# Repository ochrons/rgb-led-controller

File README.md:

rgb-led-controller
==================

Multi node controller for RGB LED strips

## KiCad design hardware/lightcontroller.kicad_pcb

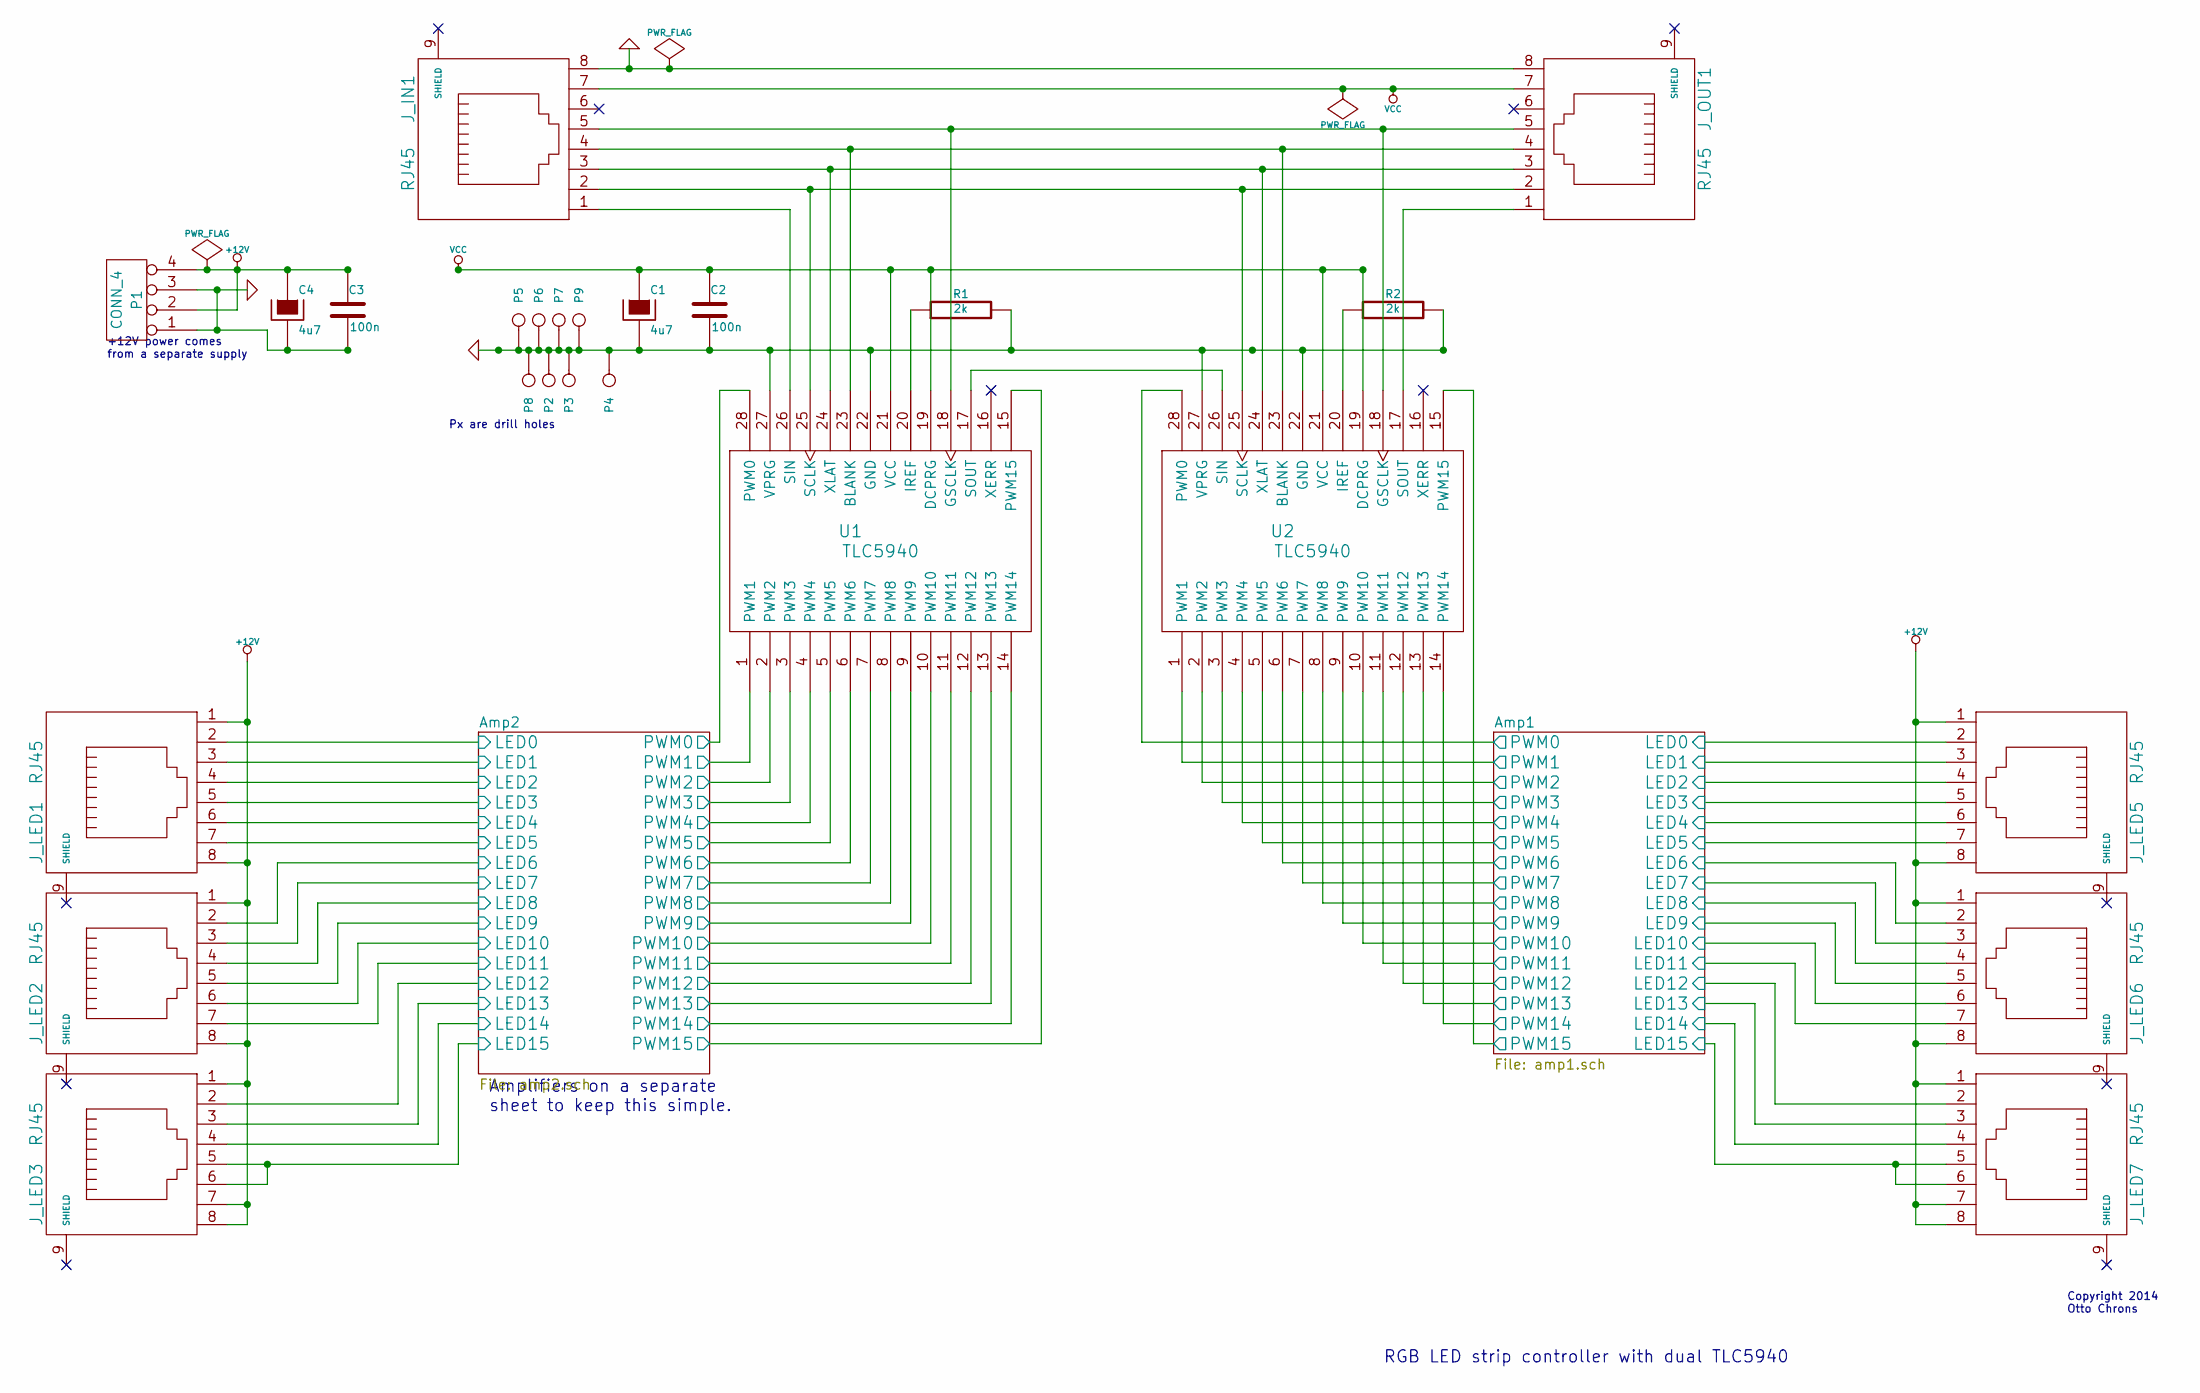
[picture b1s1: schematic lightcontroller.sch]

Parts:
C1, C4: 4u7
C2, C3: 100n
J_IN1: RJ45
J_LED1, J_LED2, J_LED3, J_LED5, J_LED6, J_LED7: RJ45
J_OUT1: RJ45
P1: CONN_4
P2, P3, P4, P6, P7, P9: CONN_1
P5, P8: CONN_1
R1, R2: 2k
U1, U2: TLC5940

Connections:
+12V: C3.1, C4.1, J_LED1.1, J_LED1.8, J_LED2.1, J_LED2.8, J_LED3.1, J_LED3.7, J_LED3.8, J_LED5.1, J_LED5.8, J_LED6.1, J_LED6.8, J_LED7.1, J_LED7.7, J_LED7.8, P1.2, P1.4; also elsewhere on the board
/Amp1/LED0: J_LED5.2; also elsewhere on the board
/Amp1/LED1: J_LED5.3; also elsewhere on the board
/Amp1/LED2: J_LED5.4; also elsewhere on the board
/Amp1/LED3: J_LED5.5; also elsewhere on the board
/Amp1/LED4: J_LED5.6; also elsewhere on the board
/Amp1/LED5: J_LED5.7; also elsewhere on the board
/Amp1/LED6: J_LED6.2; also elsewhere on the board
/Amp1/LED7: J_LED6.3; also elsewhere on the board
/Amp1/LED8: J_LED6.4; also elsewhere on the board
/Amp1/LED9: J_LED6.5; also elsewhere on the board
/Amp1/LED10: J_LED6.6; also elsewhere on the board
/Amp1/LED11: J_LED6.7; also elsewhere on the board
/Amp1/LED12: J_LED7.2; also elsewhere on the board
/Amp1/LED13: J_LED7.3; also elsewhere on the board
/Amp1/LED14: J_LED7.4; also elsewhere on the board
/Amp1/LED15: J_LED7.5, J_LED7.6; also elsewhere on the board
/Amp1/PWM0: U2.28 (PWM0); also elsewhere on the board
/Amp1/PWM1: U2.1 (PWM1); also elsewhere on the board
/Amp1/PWM2: U2.2 (PWM2); also elsewhere on the board
/Amp1/PWM3: U2.3 (PWM3); also elsewhere on the board
/Amp1/PWM4: U2.4 (PWM4); also elsewhere on the board
/Amp1/PWM5: U2.5 (PWM5); also elsewhere on the board
/Amp1/PWM6: U2.6 (PWM6); also elsewhere on the board
/Amp1/PWM7: U2.7 (PWM7); also elsewhere on the board
/Amp1/PWM8: U2.8 (PWM8); also elsewhere on the board
/Amp1/PWM9: U2.9 (PWM9); also elsewhere on the board
/Amp1/PWM10: U2.10 (PWM10); also elsewhere on the board
/Amp1/PWM11: U2.11 (PWM11); also elsewhere on the board
/Amp1/PWM12: U2.12 (PWM12); also elsewhere on the board
/Amp1/PWM13: U2.13 (PWM13); also elsewhere on the board
/Amp1/PWM14: U2.14 (PWM14); also elsewhere on the board
/Amp1/PWM15: U2.15 (PWM15); also elsewhere on the board
/Amp2/LED0: J_LED1.2; also elsewhere on the board
/Amp2/LED1: J_LED1.3; also elsewhere on the board
/Amp2/LED2: J_LED1.4; also elsewhere on the board
/Amp2/LED3: J_LED1.5; also elsewhere on the board
/Amp2/LED4: J_LED1.6; also elsewhere on the board
/Amp2/LED5: J_LED1.7; also elsewhere on the board
/Amp2/LED6: J_LED2.2; also elsewhere on the board
/Amp2/LED7: J_LED2.3; also elsewhere on the board
/Amp2/LED8: J_LED2.4; also elsewhere on the board
/Amp2/LED9: J_LED2.5; also elsewhere on the board
/Amp2/LED10: J_LED2.6; also elsewhere on the board
/Amp2/LED11: J_LED2.7; also elsewhere on the board
/Amp2/LED12: J_LED3.2; also elsewhere on the board
/Amp2/LED13: J_LED3.3; also elsewhere on the board
/Amp2/LED14: J_LED3.4; also elsewhere on the board
/Amp2/LED15: J_LED3.5, J_LED3.6; also elsewhere on the board
/Amp2/PWM0: U1.28 (PWM0); also elsewhere on the board
/Amp2/PWM1: U1.1 (PWM1); also elsewhere on the board
/Amp2/PWM2: U1.2 (PWM2); also elsewhere on the board
/Amp2/PWM3: U1.3 (PWM3); also elsewhere on the board
/Amp2/PWM4: U1.4 (PWM4); also elsewhere on the board
/Amp2/PWM5: U1.5 (PWM5); also elsewhere on the board
/Amp2/PWM6: U1.6 (PWM6); also elsewhere on the board
/Amp2/PWM7: U1.7 (PWM7); also elsewhere on the board
/Amp2/PWM8: U1.8 (PWM8); also elsewhere on the board
/Amp2/PWM9: U1.9 (PWM9); also elsewhere on the board
/Amp2/PWM10: U1.10 (PWM10); also elsewhere on the board
/Amp2/PWM11: U1.11 (PWM11); also elsewhere on the board
/Amp2/PWM12: U1.12 (PWM12); also elsewhere on the board
/Amp2/PWM13: U1.13 (PWM13); also elsewhere on the board
/Amp2/PWM14: U1.14 (PWM14); also elsewhere on the board
/Amp2/PWM15: U1.15 (PWM15); also elsewhere on the board
GND: C1.2, C2.2, C3.2, C4.2, J_IN1.8, J_OUT1.8, P1.1, P1.3, P2.1, P3.1, P4.1, P5.1, P6.1, P7.1, P8.1, P9.1, R1.2, R2.2, U1.22 (GND), U1.27 (VPRG), U2.22 (GND), U2.27 (VPRG); also elsewhere on the board
unnamed: J_OUT1.1, U2.17 (SOUT)
unnamed: J_IN1.1, U1.26 (SIN)
unnamed: R1.1, U1.20 (IREF)
unnamed: J_IN1.5, J_OUT1.5, U1.18 (GSCLK), U2.18 (GSCLK)
unnamed: U1.17 (SOUT), U2.26 (SIN)
unnamed: J_IN1.4, J_OUT1.4, U1.23 (BLANK), U2.23 (BLANK)
unnamed: R2.1, U2.20 (IREF)
unnamed: J_IN1.3, J_OUT1.3, U1.24 (XLAT), U2.24 (XLAT)
unnamed: J_IN1.2, J_OUT1.2, U1.25 (SCLK), U2.25 (SCLK)
VCC: C1.1, C2.1, J_IN1.7, J_OUT1.7, U1.19 (DCPRG), U1.21 (VCC), U2.19 (DCPRG), U2.21 (VCC)

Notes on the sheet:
RGB LED strip controller with dual TLC5940
Px are drill holes
Amplifiers on a separate sheet to keep this simple.
+12V power comes from a separate supply
Copyright 2014 Otto Chrons

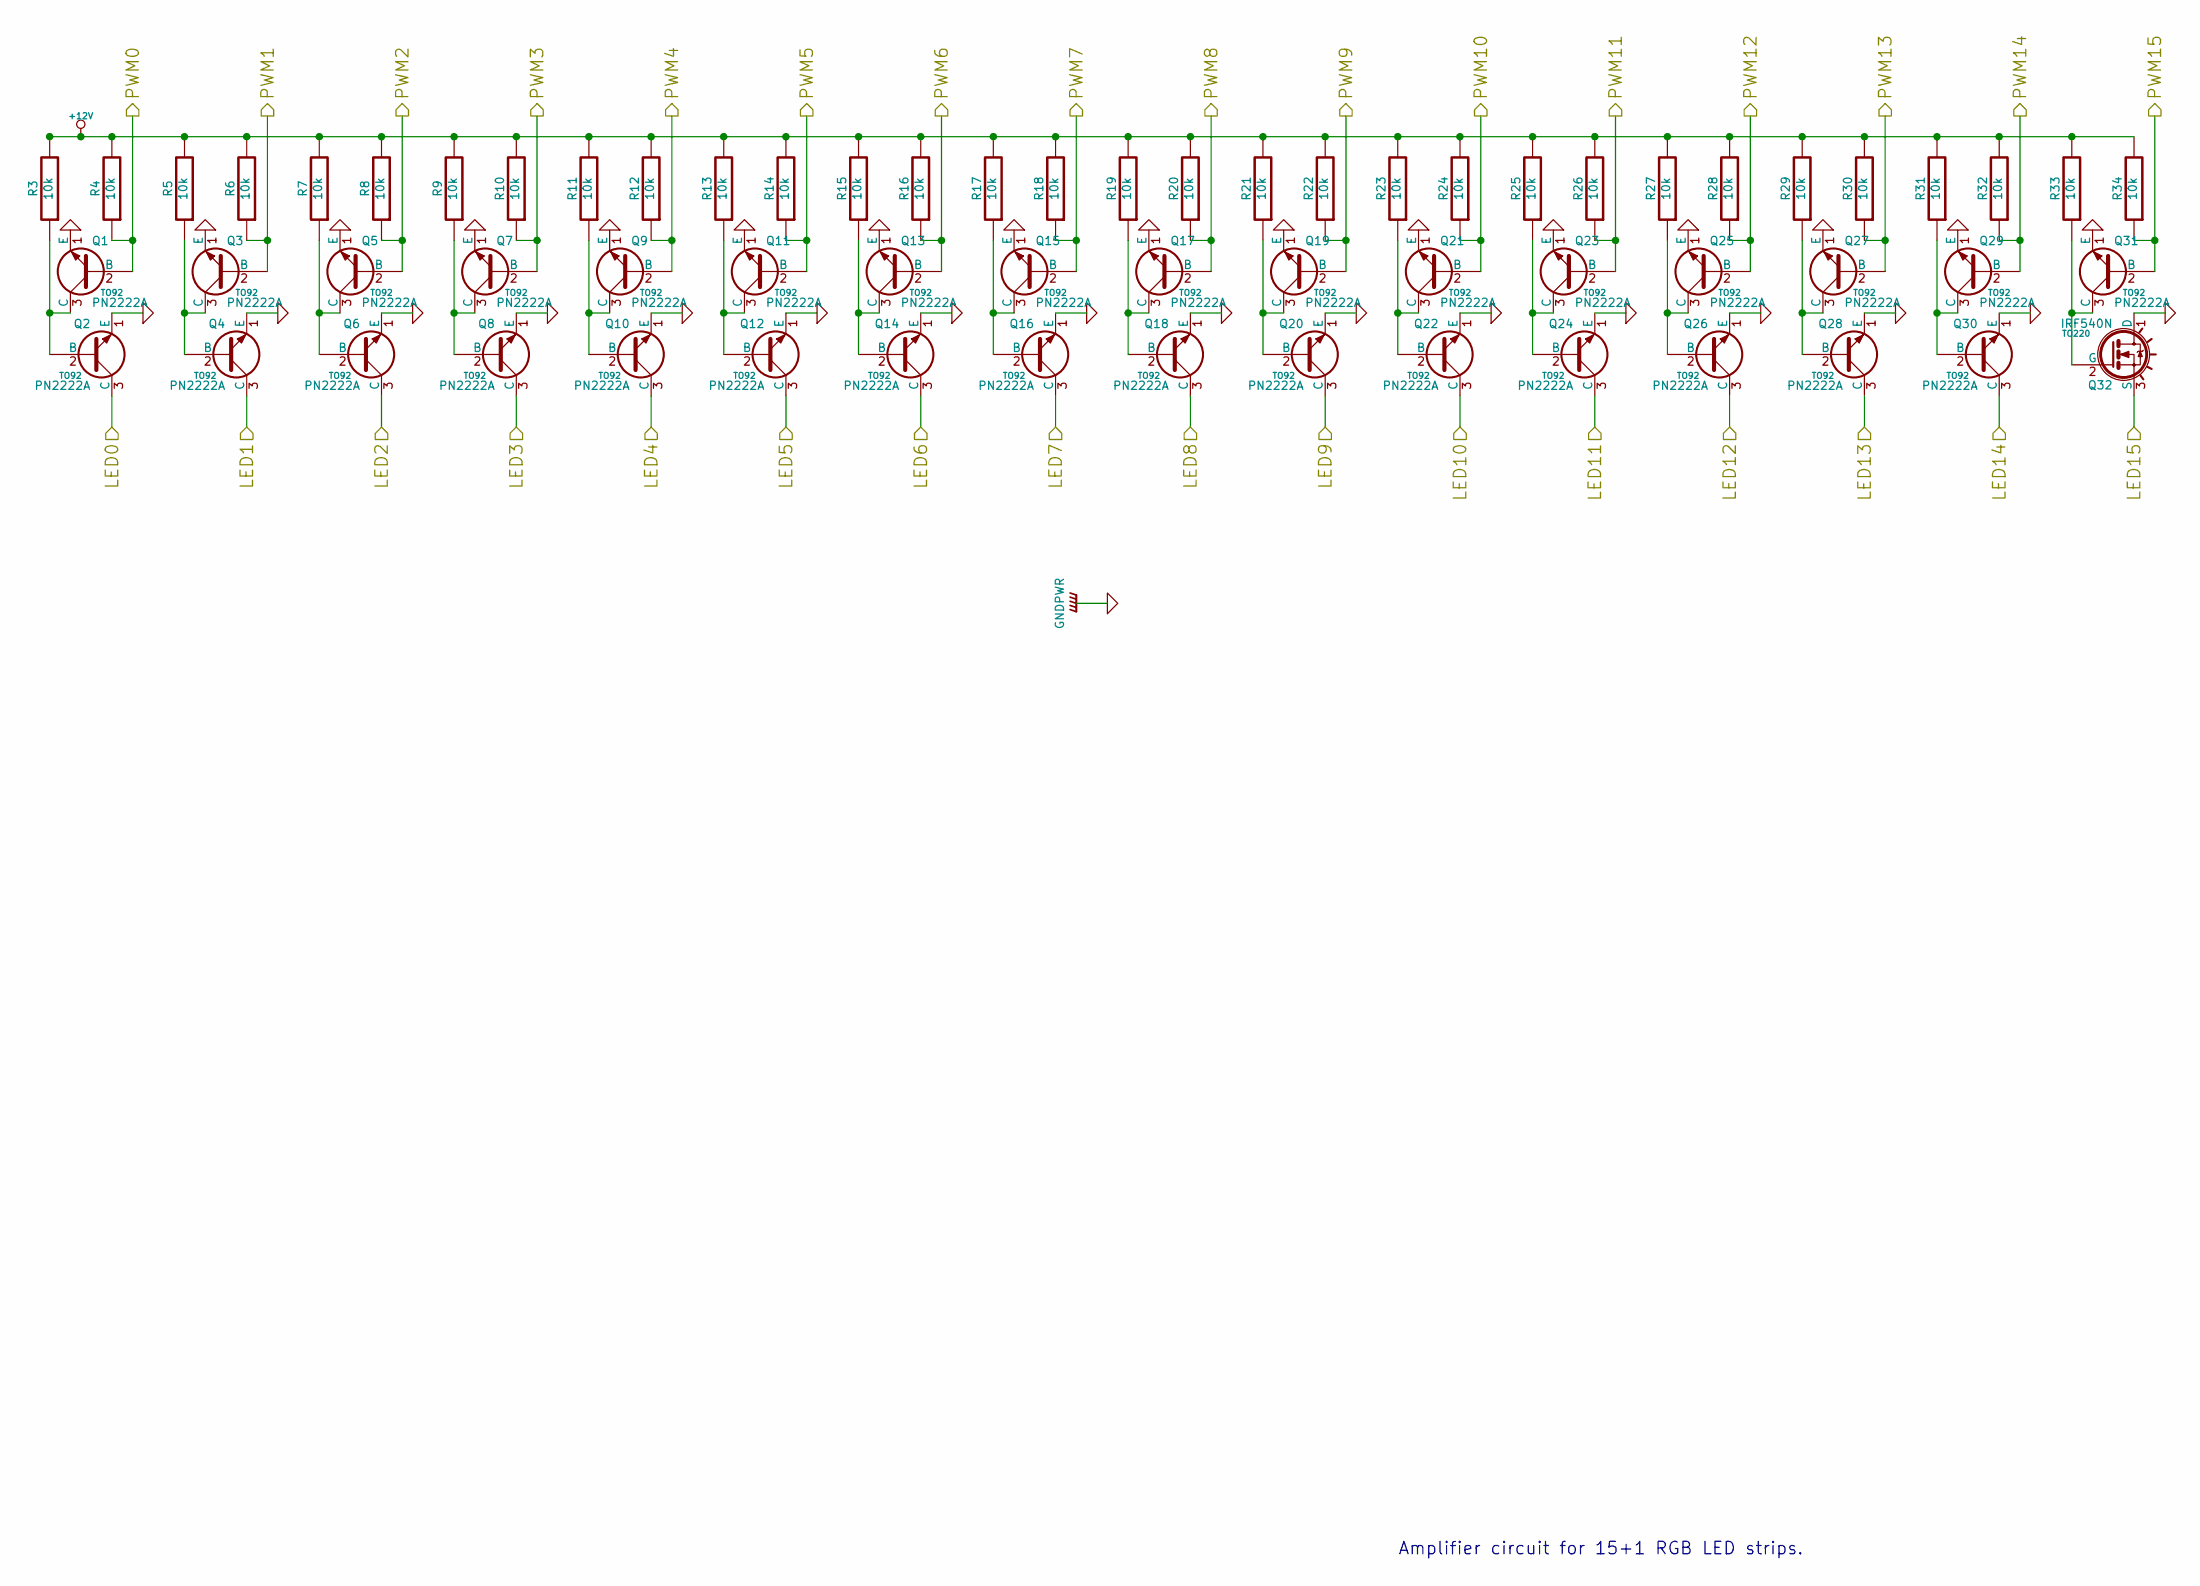
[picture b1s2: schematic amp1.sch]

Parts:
Q1, Q2, Q3, Q4, Q5, Q6, Q7, Q8, Q9, Q10, Q11, Q12, Q13, Q14, Q15, Q16, Q17, Q18, Q19, Q20, Q21, Q22, Q23, Q24, Q25, Q26, Q27, Q28, Q29, Q30, Q31: PN2222A; TO92
Q32: IRF540N; TO220
R3, R4, R5, R6, R7, R8, R9, R10, R11, R12, R13, R14, R15, R16, R17, R18, R19, R20, R21, R22, R23, R24, R25, R26, R27, R28, R29, R30, R31, R32, R33, R34: 10k

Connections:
+12V: R3.2, R4.2, R5.2, R6.2, R7.2, R8.2, R9.2, R10.2, R11.2, R12.2, R13.2, R14.2, R15.2, R16.2, R17.2, R18.2, R19.2, R20.2, R21.2, R22.2, R23.2, R24.2, R25.2, R26.2, R27.2, R28.2, R29.2, R30.2, R31.2, R32.2, R33.2, R34.2; also elsewhere on the board
/Amp1/LED0: Q2.3 (C); also elsewhere on the board
/Amp1/LED1: Q4.3 (C); also elsewhere on the board
/Amp1/LED2: Q6.3 (C); also elsewhere on the board
/Amp1/LED3: Q8.3 (C); also elsewhere on the board
/Amp1/LED4: Q10.3 (C); also elsewhere on the board
/Amp1/LED5: Q12.3 (C); also elsewhere on the board
/Amp1/LED6: Q14.3 (C); also elsewhere on the board
/Amp1/LED7: Q16.3 (C); also elsewhere on the board
/Amp1/LED8: Q18.3 (C); also elsewhere on the board
/Amp1/LED9: Q20.3 (C); also elsewhere on the board
/Amp1/LED10: Q22.3 (C); also elsewhere on the board
/Amp1/LED11: Q24.3 (C); also elsewhere on the board
/Amp1/LED12: Q26.3 (C); also elsewhere on the board
/Amp1/LED13: Q28.3 (C); also elsewhere on the board
/Amp1/LED14: Q30.3 (C); also elsewhere on the board
/Amp1/LED15: Q32.3 (S); also elsewhere on the board
/Amp1/PWM0: Q1.2 (B), R4.1; also elsewhere on the board
/Amp1/PWM1: Q3.2 (B), R6.1; also elsewhere on the board
/Amp1/PWM2: Q5.2 (B), R8.1; also elsewhere on the board
/Amp1/PWM3: Q7.2 (B), R10.1; also elsewhere on the board
/Amp1/PWM4: Q9.2 (B), R12.1; also elsewhere on the board
/Amp1/PWM5: Q11.2 (B), R14.1; also elsewhere on the board
/Amp1/PWM6: Q13.2 (B), R16.1; also elsewhere on the board
/Amp1/PWM7: Q15.2 (B), R18.1; also elsewhere on the board
/Amp1/PWM8: Q17.2 (B), R20.1; also elsewhere on the board
/Amp1/PWM9: Q19.2 (B), R22.1; also elsewhere on the board
/Amp1/PWM10: Q21.2 (B), R24.1; also elsewhere on the board
/Amp1/PWM11: Q23.2 (B), R26.1; also elsewhere on the board
/Amp1/PWM12: Q25.2 (B), R28.1; also elsewhere on the board
/Amp1/PWM13: Q27.2 (B), R30.1; also elsewhere on the board
/Amp1/PWM14: Q29.2 (B), R32.1; also elsewhere on the board
/Amp1/PWM15: Q31.2 (B), R34.1; also elsewhere on the board
GND: Q1.1 (E), Q2.1 (E), Q3.1 (E), Q4.1 (E), Q5.1 (E), Q6.1 (E), Q7.1 (E), Q8.1 (E), Q9.1 (E), Q10.1 (E), Q11.1 (E), Q12.1 (E), Q13.1 (E), Q14.1 (E), Q15.1 (E), Q16.1 (E), Q17.1 (E), Q18.1 (E), Q19.1 (E), Q20.1 (E), Q21.1 (E), Q22.1 (E), Q23.1 (E), Q24.1 (E), Q25.1 (E), Q26.1 (E), Q27.1 (E), Q28.1 (E), Q29.1 (E), Q30.1 (E), Q31.1 (E), Q32.1 (D); also elsewhere on the board
unnamed: Q21.3 (C), Q22.2 (B), R23.1
unnamed: Q23.3 (C), Q24.2 (B), R25.1
unnamed: Q17.3 (C), Q18.2 (B), R19.1
unnamed: Q19.3 (C), Q20.2 (B), R21.1
unnamed: Q31.3 (C), Q32.2 (G), R33.1
unnamed: Q29.3 (C), Q30.2 (B), R31.1
unnamed: Q25.3 (C), Q26.2 (B), R27.1
unnamed: Q27.3 (C), Q28.2 (B), R29.1
unnamed: Q5.3 (C), Q6.2 (B), R7.1
unnamed: Q7.3 (C), Q8.2 (B), R9.1
unnamed: Q1.3 (C), Q2.2 (B), R3.1
unnamed: Q3.3 (C), Q4.2 (B), R5.1
unnamed: Q13.3 (C), Q14.2 (B), R15.1
unnamed: Q15.3 (C), Q16.2 (B), R17.1
unnamed: Q9.3 (C), Q10.2 (B), R11.1
unnamed: Q11.3 (C), Q12.2 (B), R13.1

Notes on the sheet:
Amplifier circuit for 15+1 RGB LED strips.

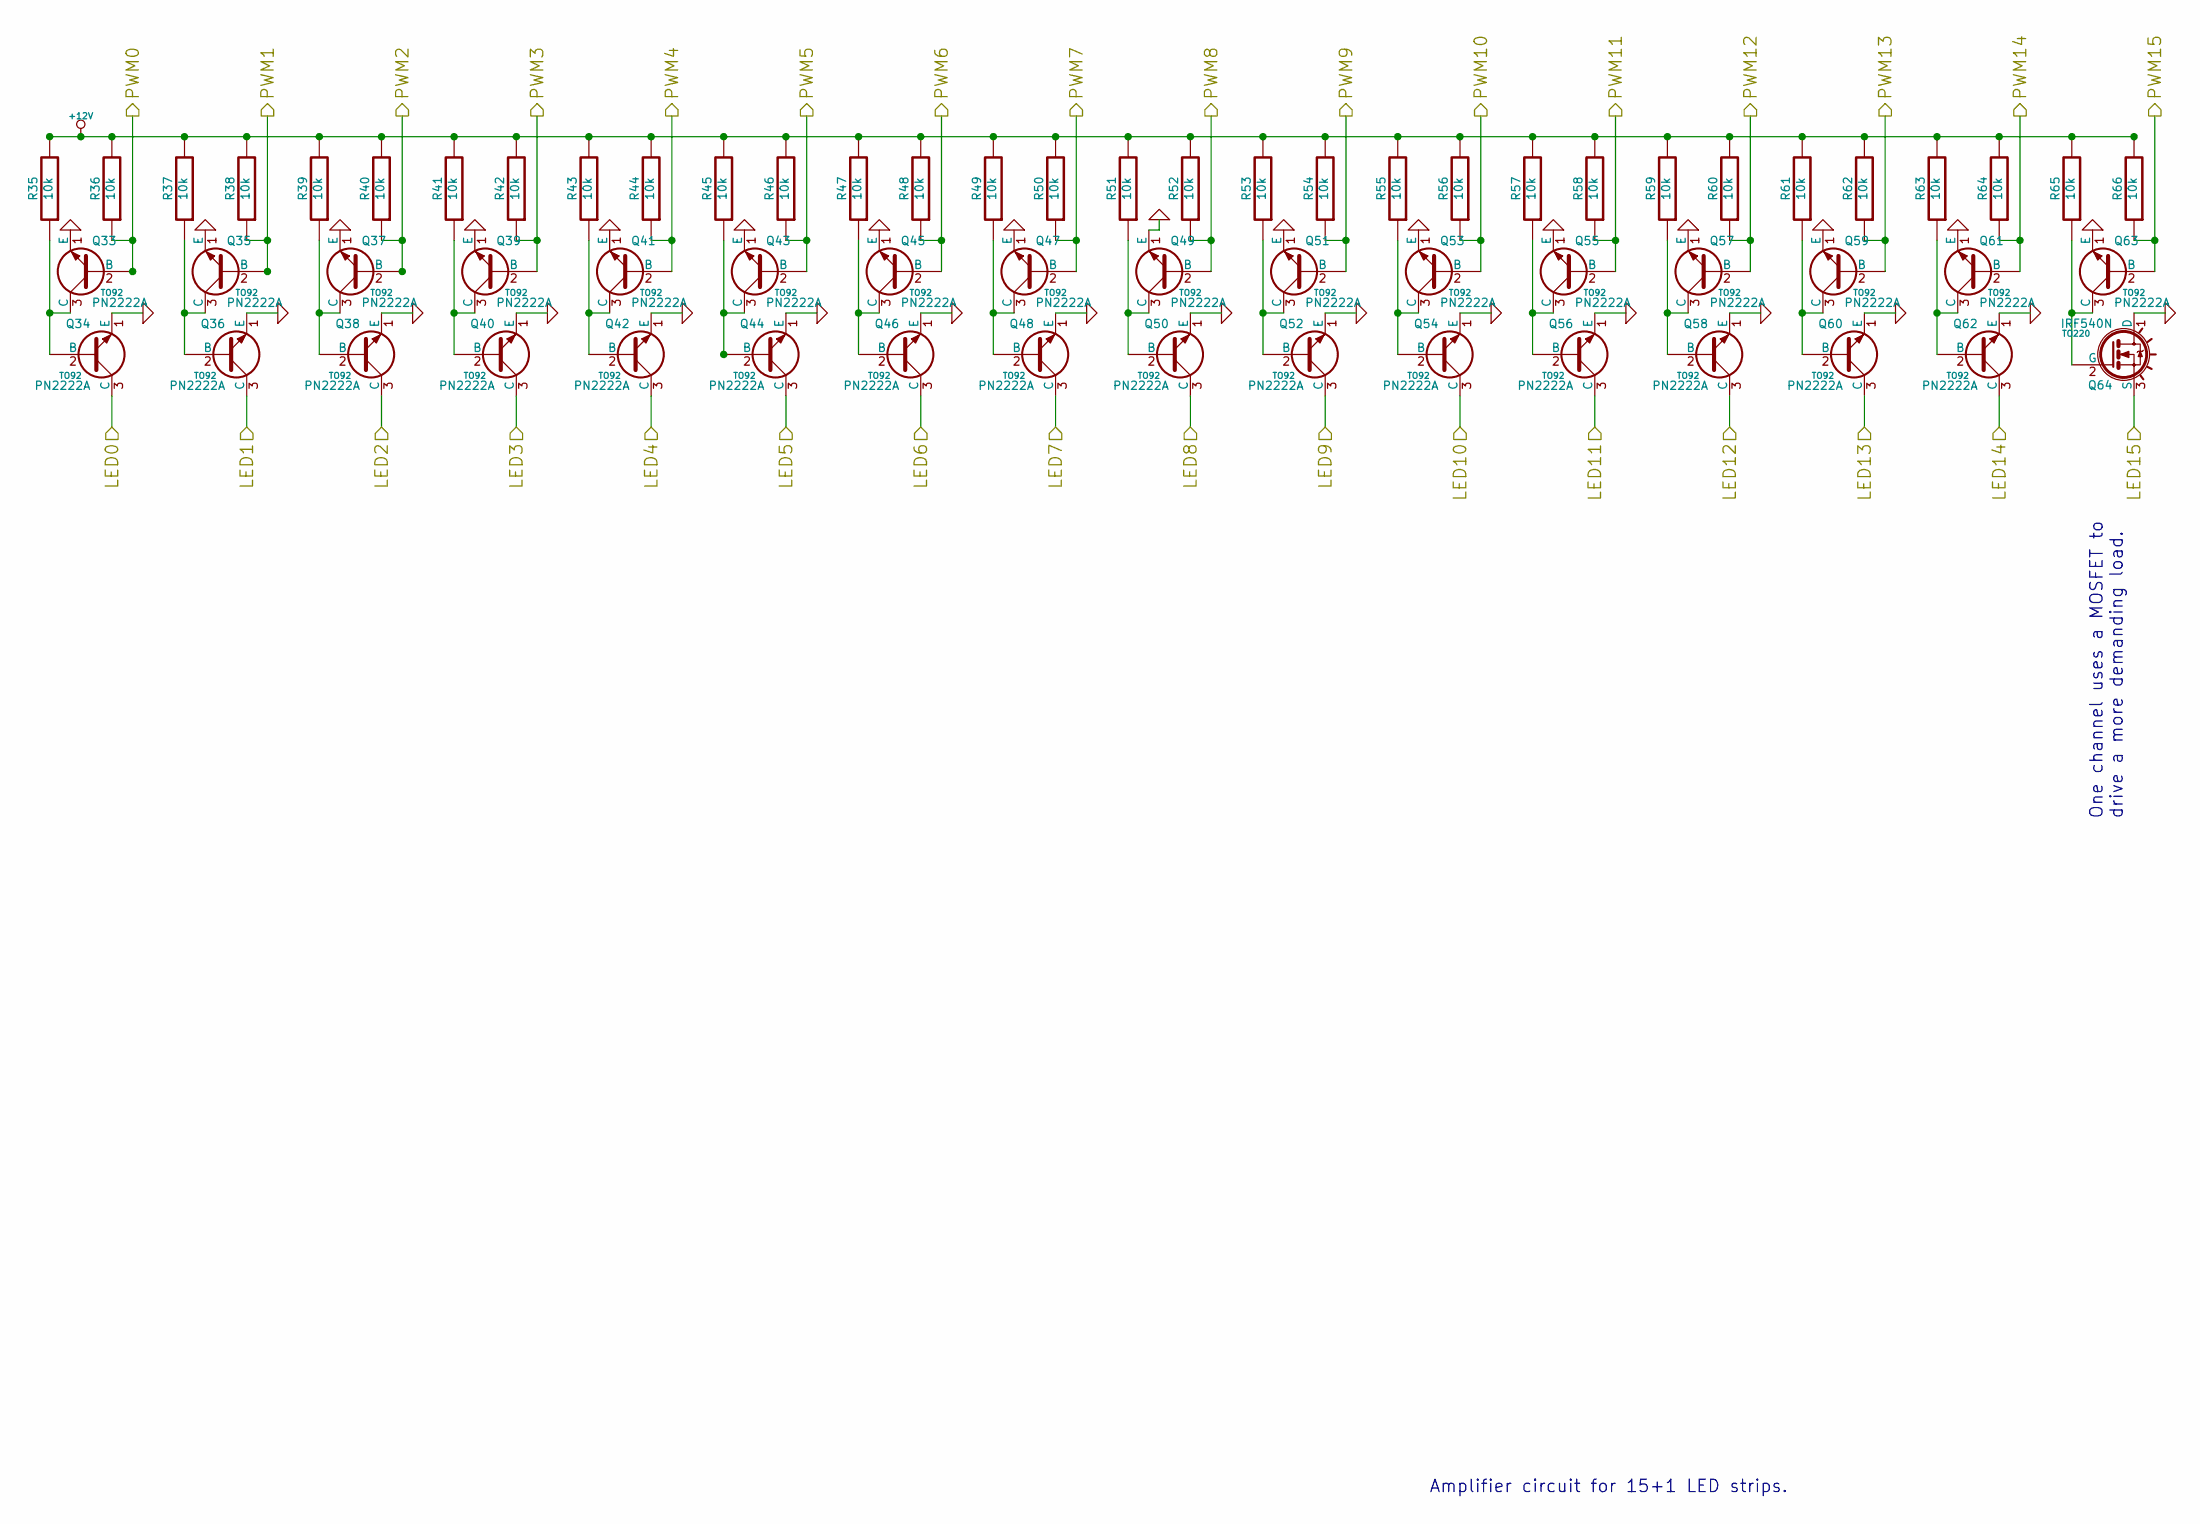
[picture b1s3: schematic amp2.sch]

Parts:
Q33, Q34, Q35, Q36, Q37, Q38, Q39, Q40, Q41, Q42, Q43, Q44, Q45, Q46, Q47, Q48, Q49, Q50, Q51, Q52, Q53, Q54, Q55, Q56, Q57, Q58, Q59, Q60, Q61, Q62, Q63: PN2222A; TO92
Q64: IRF540N; TO220
R35, R36, R37, R38, R39, R40, R41, R42, R43, R44, R45, R46, R47, R48, R49, R50, R51, R52, R53, R54, R55, R56, R57, R58, R59, R60, R61, R62, R63, R64, R65, R66: 10k

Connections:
+12V: R35.2, R36.2, R37.2, R38.2, R39.2, R40.2, R41.2, R42.2, R43.2, R44.2, R45.2, R46.2, R47.2, R48.2, R49.2, R50.2, R51.2, R52.2, R53.2, R54.2, R55.2, R56.2, R57.2, R58.2, R59.2, R60.2, R61.2, R62.2, R63.2, R64.2, R65.2, R66.2; also elsewhere on the board
/Amp2/LED0: Q34.3 (C); also elsewhere on the board
/Amp2/LED1: Q36.3 (C); also elsewhere on the board
/Amp2/LED2: Q38.3 (C); also elsewhere on the board
/Amp2/LED3: Q40.3 (C); also elsewhere on the board
/Amp2/LED4: Q42.3 (C); also elsewhere on the board
/Amp2/LED5: Q44.3 (C); also elsewhere on the board
/Amp2/LED6: Q46.3 (C); also elsewhere on the board
/Amp2/LED7: Q48.3 (C); also elsewhere on the board
/Amp2/LED8: Q50.3 (C); also elsewhere on the board
/Amp2/LED9: Q52.3 (C); also elsewhere on the board
/Amp2/LED10: Q54.3 (C); also elsewhere on the board
/Amp2/LED11: Q56.3 (C); also elsewhere on the board
/Amp2/LED12: Q58.3 (C); also elsewhere on the board
/Amp2/LED13: Q60.3 (C); also elsewhere on the board
/Amp2/LED14: Q62.3 (C); also elsewhere on the board
/Amp2/LED15: Q64.3 (S); also elsewhere on the board
/Amp2/PWM0: Q33.2 (B), R36.1; also elsewhere on the board
/Amp2/PWM1: Q35.2 (B), R38.1; also elsewhere on the board
/Amp2/PWM2: Q37.2 (B), R40.1; also elsewhere on the board
/Amp2/PWM3: Q39.2 (B), R42.1; also elsewhere on the board
/Amp2/PWM4: Q41.2 (B), R44.1; also elsewhere on the board
/Amp2/PWM5: Q43.2 (B), R46.1; also elsewhere on the board
/Amp2/PWM6: Q45.2 (B), R48.1; also elsewhere on the board
/Amp2/PWM7: Q47.2 (B), R50.1; also elsewhere on the board
/Amp2/PWM8: Q49.2 (B), R52.1; also elsewhere on the board
/Amp2/PWM9: Q51.2 (B), R54.1; also elsewhere on the board
/Amp2/PWM10: Q53.2 (B), R56.1; also elsewhere on the board
/Amp2/PWM11: Q55.2 (B), R58.1; also elsewhere on the board
/Amp2/PWM12: Q57.2 (B), R60.1; also elsewhere on the board
/Amp2/PWM13: Q59.2 (B), R62.1; also elsewhere on the board
/Amp2/PWM14: Q61.2 (B), R64.1; also elsewhere on the board
/Amp2/PWM15: Q63.2 (B), R66.1; also elsewhere on the board
GND: Q33.1 (E), Q34.1 (E), Q35.1 (E), Q36.1 (E), Q37.1 (E), Q38.1 (E), Q39.1 (E), Q40.1 (E), Q41.1 (E), Q42.1 (E), Q43.1 (E), Q44.1 (E), Q45.1 (E), Q46.1 (E), Q47.1 (E), Q48.1 (E), Q49.1 (E), Q50.1 (E), Q51.1 (E), Q52.1 (E), Q53.1 (E), Q54.1 (E), Q55.1 (E), Q56.1 (E), Q57.1 (E), Q58.1 (E), Q59.1 (E), Q60.1 (E), Q61.1 (E), Q62.1 (E), Q63.1 (E), Q64.1 (D); also elsewhere on the board
unnamed: Q37.3 (C), Q38.2 (B), R39.1
unnamed: Q39.3 (C), Q40.2 (B), R41.1
unnamed: Q35.3 (C), Q36.2 (B), R37.1
unnamed: Q43.3 (C), Q44.2 (B), R45.1
unnamed: Q45.3 (C), Q46.2 (B), R47.1
unnamed: Q41.3 (C), Q42.2 (B), R43.1
unnamed: Q33.3 (C), Q34.2 (B), R35.1
unnamed: Q63.3 (C), Q64.2 (G), R65.1
unnamed: Q61.3 (C), Q62.2 (B), R63.1
unnamed: Q59.3 (C), Q60.2 (B), R61.1
unnamed: Q49.3 (C), Q50.2 (B), R51.1
unnamed: Q51.3 (C), Q52.2 (B), R53.1
unnamed: Q47.3 (C), Q48.2 (B), R49.1
unnamed: Q55.3 (C), Q56.2 (B), R57.1
unnamed: Q57.3 (C), Q58.2 (B), R59.1
unnamed: Q53.3 (C), Q54.2 (B), R55.1

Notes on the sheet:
Amplifier circuit for 15+1 LED strips.
One channel uses a MOSFET to drive a more demanding load.

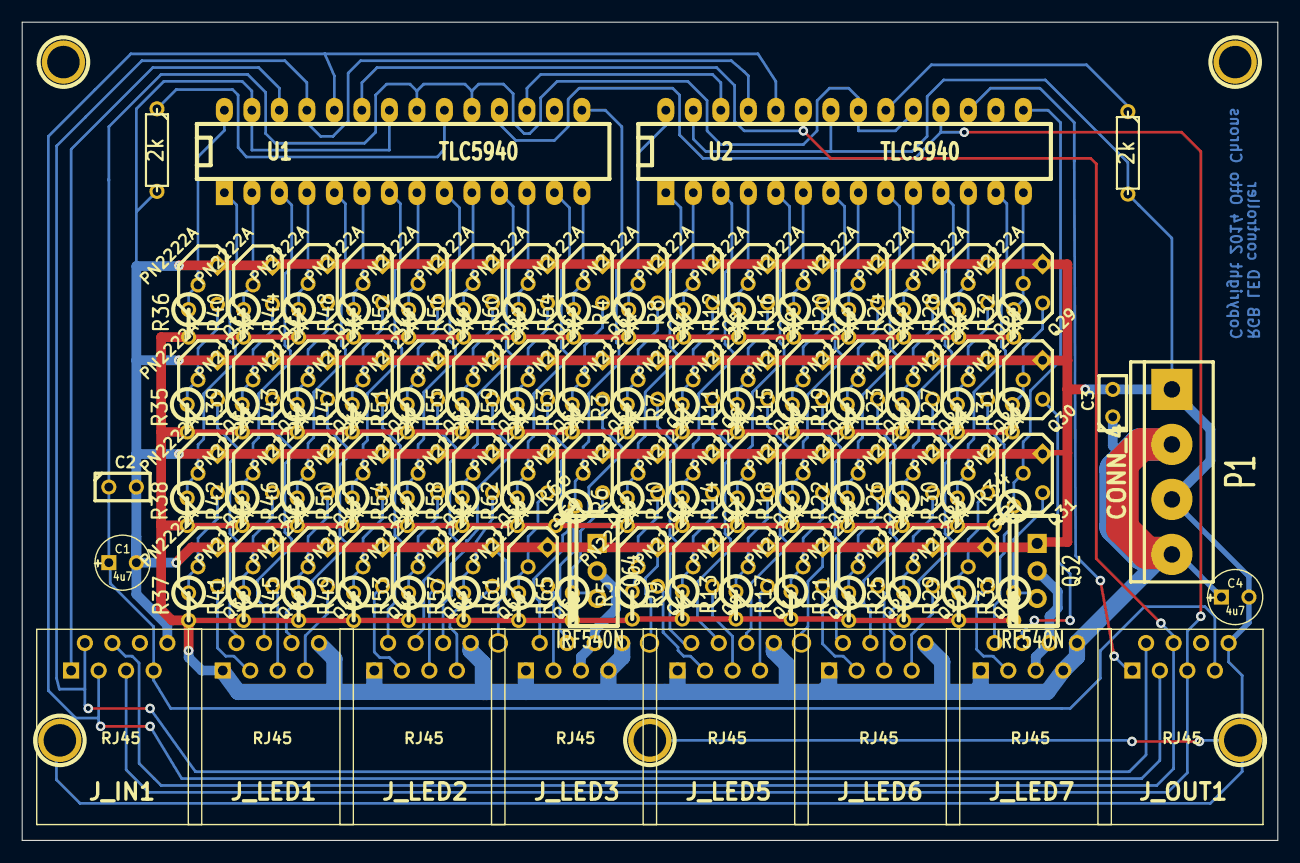
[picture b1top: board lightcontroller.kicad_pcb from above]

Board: 2 copper layers, 116.0 x 75.6 mm, 153 parts (0 on the bottom side), 108 nets.

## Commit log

2014-04-03 First revision of the hardware design.
2014-04-03 Added PDF and PNG images of the design.
